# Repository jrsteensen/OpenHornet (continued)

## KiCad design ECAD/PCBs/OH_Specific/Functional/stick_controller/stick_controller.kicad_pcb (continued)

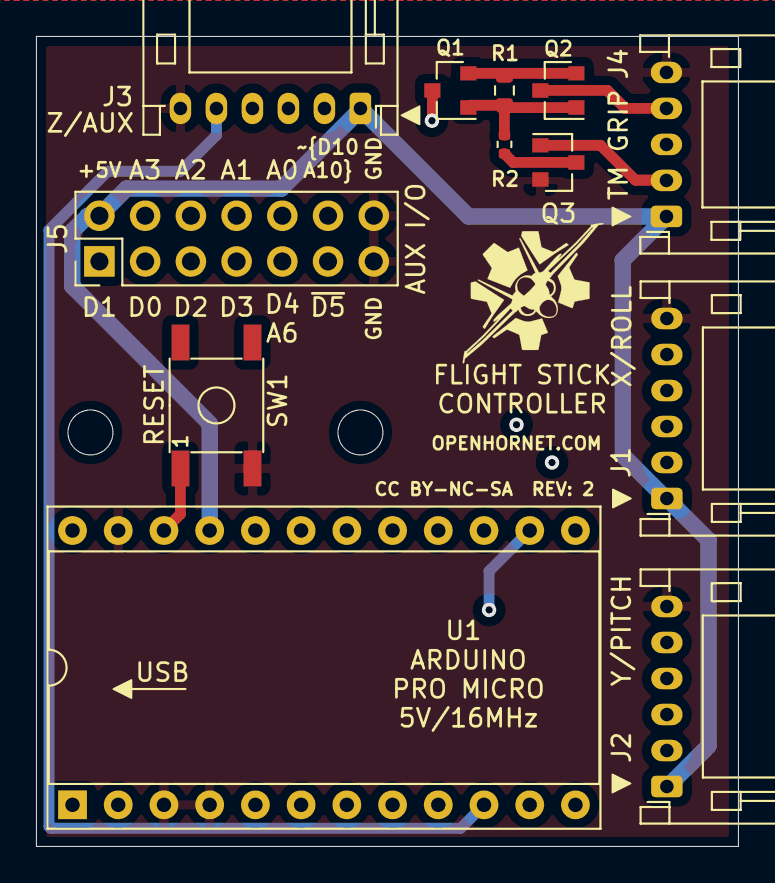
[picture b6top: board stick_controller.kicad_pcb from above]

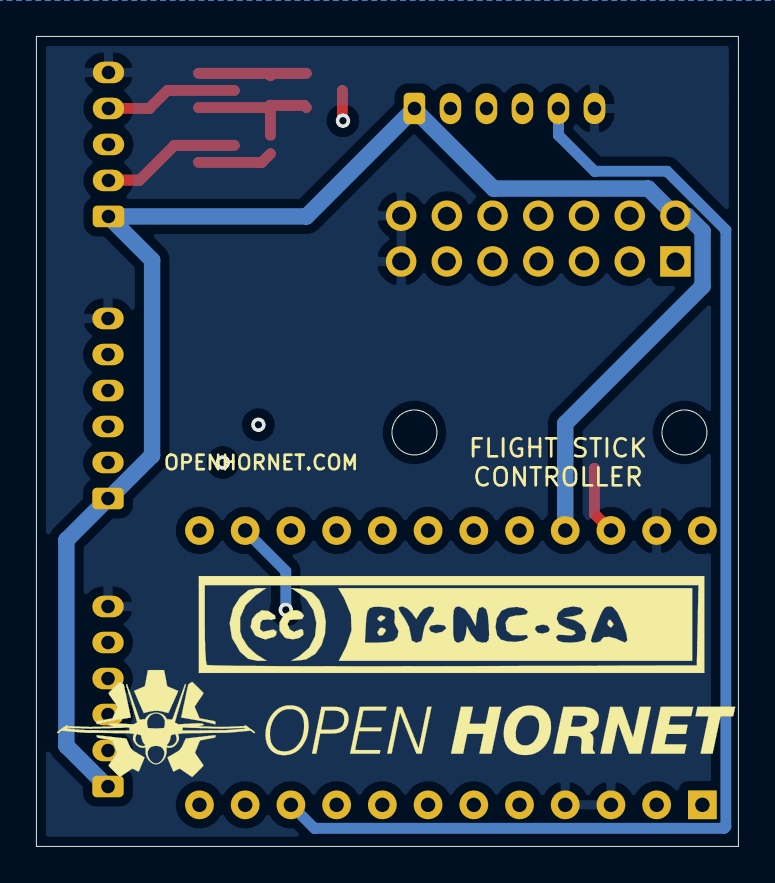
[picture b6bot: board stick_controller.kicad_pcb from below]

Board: 4 copper layers, 39.0 x 45.0 mm, 17 parts (2 on the bottom side), 25 nets.
